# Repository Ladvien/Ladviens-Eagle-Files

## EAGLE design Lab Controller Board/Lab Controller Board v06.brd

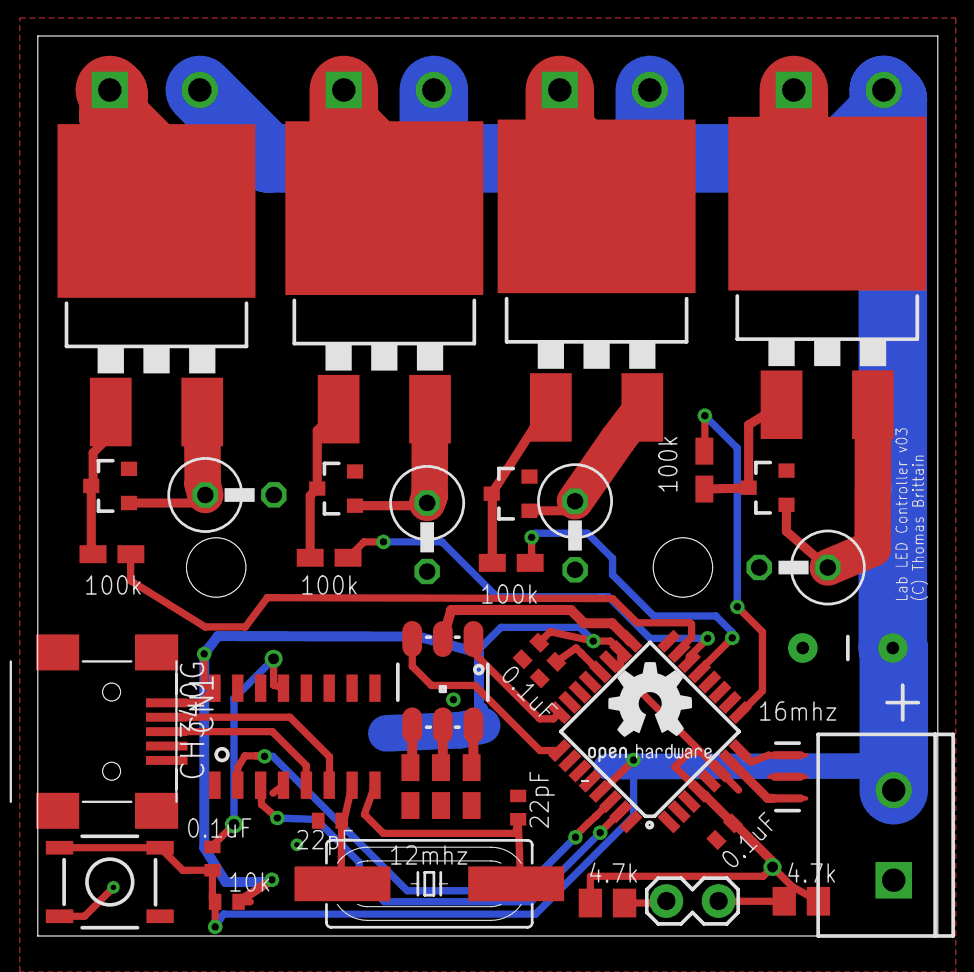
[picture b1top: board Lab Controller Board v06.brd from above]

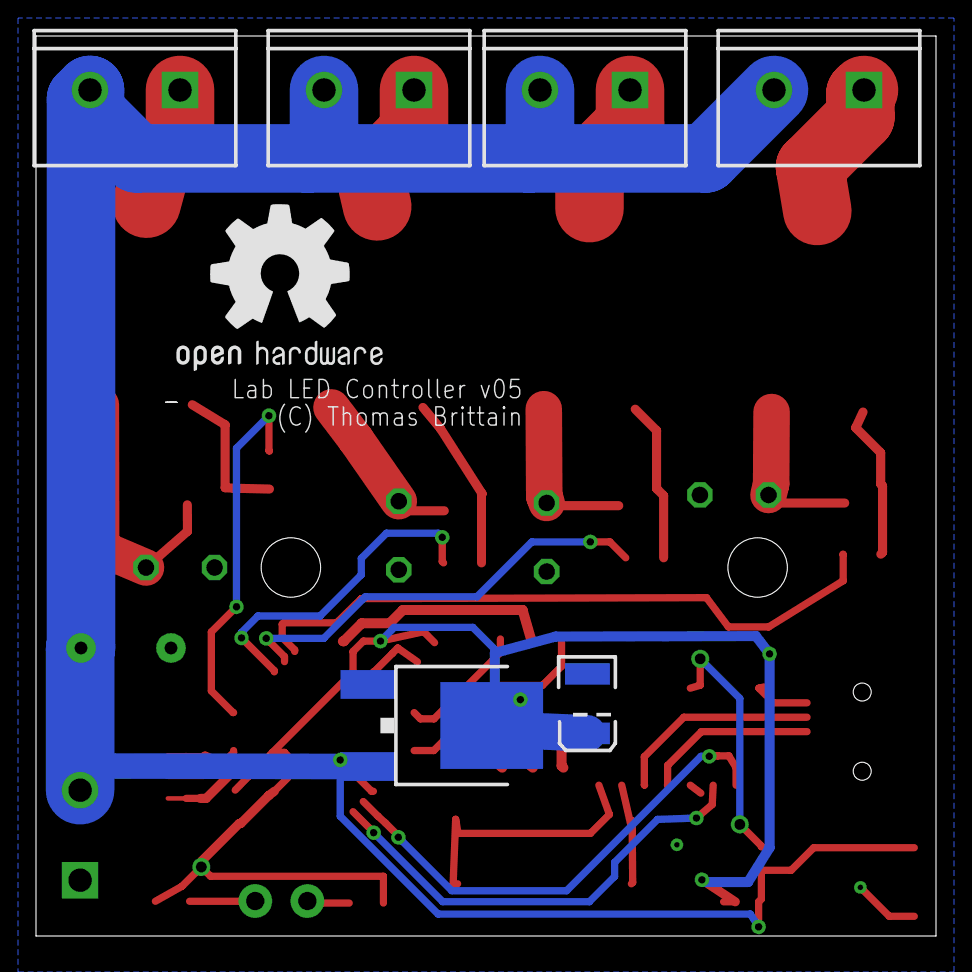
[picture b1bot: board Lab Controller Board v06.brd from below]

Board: 2 copper layers, 50.0 x 50.0 mm, 48 parts (7 on the bottom side), 38 nets.

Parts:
C1: big; CAP-PTH-5MM
C2: 10uF; EIA3528
C3, C4, C5, C8: 0.1uF; C0402
C6, C7: 22pF; C0402
CN1: USB-MINIB
FQP30N06L: 100A/100V; TO-263/D2PAK
GOLD_ORB_SM1: OSHWLOGO_GOLD_ORB_MED; OSHW1
GOLD_ORB_SM2: OSHWLOGO_GOLD_ORB_SM; OSHW2
JP1, JP2, JP3, JP4, JP5: SCREWTERMINAL-5MM-2
JP8: 1X02_LOCK
LED1: LED-TRICOLOR-5050NO_IC; LED-TRICOLOR-5050
MC7805CD2TR4: V_REG_MC33269DT; DPAK
Q1: HC49UP
Q2, Q4, Q6, Q8: MMBT5088; SOT23-3
Q3, Q5, Q7: 100A/100V; TO-263/D2PAK
R1, R3, R5, R7, R11, R12, R13: 100k; R0805W
R2, R4, R6, R8: .75Ohm; 0411V
R9, R10: 4.7k; M0805
R14: 10k; R0402
S1: TAC_SWITCHSMD; TACTILE-SWITCH-SMD
STANDOFF1, STANDOFF2: STAND-OFF
U1: ATMEGA328P_TQFP; TQFP32-08
U2: CH340G; SOIC16
Y1: 16MHZ; RESONATOR-SMD

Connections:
5: R5.1, U1.9
9: R7.1, U1.13
10: R1.1, U1.14
11: R3.1, U1.15
12V: C1.1, JP1.2, JP2.2, JP3.2, JP4.2, JP5.2, MC7805CD2TR4.3
13: LED1.2, U1.17
A1: LED1.1, U1.24
A2: LED1.3, U1.25
D+: CN1.D+, U2.5
D-: CN1.D-, U2.6
DTR: C5.1, U2.13
FET_SOURCE: FQP30N06L.3, Q2.1, R2.1
FET_SOURCE1: Q3.3, Q4.1, R4.1
FET_SOURCE2: Q5.3, Q6.1, R6.1
FET_SOURCE3: Q7.3, Q8.1, R8.1
GND: C1.2, C2.C, C3.2, C4.2, C6.2, C7.2, C8.2, CN1.GND, JP1.1, MC7805CD2TR4.1, Q2.2, Q4.2, Q6.2, Q8.2, R2.2, R4.2, R6.2, R8.2, R11.1, R12.1, R13.1, S1.1, S1.2, U1.3, U1.5, U1.21, U2.1, Y1.2
LED_DRAIN: FQP30N06L.2, JP2.1
LED_DRAIN1: JP5.1, Q3.2
LED_DRAIN2: JP4.1, Q5.2
LED_DRAIN3: JP3.1, Q7.2
unnamed: C3.1, U1.20
unnamed: U1.7, Y1.1
unnamed: LED1.4, R11.2
unnamed: LED1.6, R12.2
unnamed: LED1.5, R13.2
unnamed: U1.8, Y1.3
unnamed: C5.2, R14.1, S1.3, S1.4, U1.29
PWM_B: FQP30N06L.1, Q2.3, R1.2
PWM_B1: Q3.1, Q4.3, R3.2
PWM_B2: Q5.1, Q6.3, R5.2
PWM_B3: Q7.1, Q8.3, R7.2
SCL: JP8.1, R10.1
SDA: JP8.2, R9.1
U2_RX: U1.31, U2.3
U2_TX: U1.30, U2.2
VCC: C2.A, C4.1, C8.1, CN1.VBUS, MC7805CD2TR4.4, R9.2, R10.2, R14.2, U1.4, U1.6, U1.18, U2.16
X0: C7.1, Q1.2, U2.8
X1: C6.1, Q1.1, U2.7

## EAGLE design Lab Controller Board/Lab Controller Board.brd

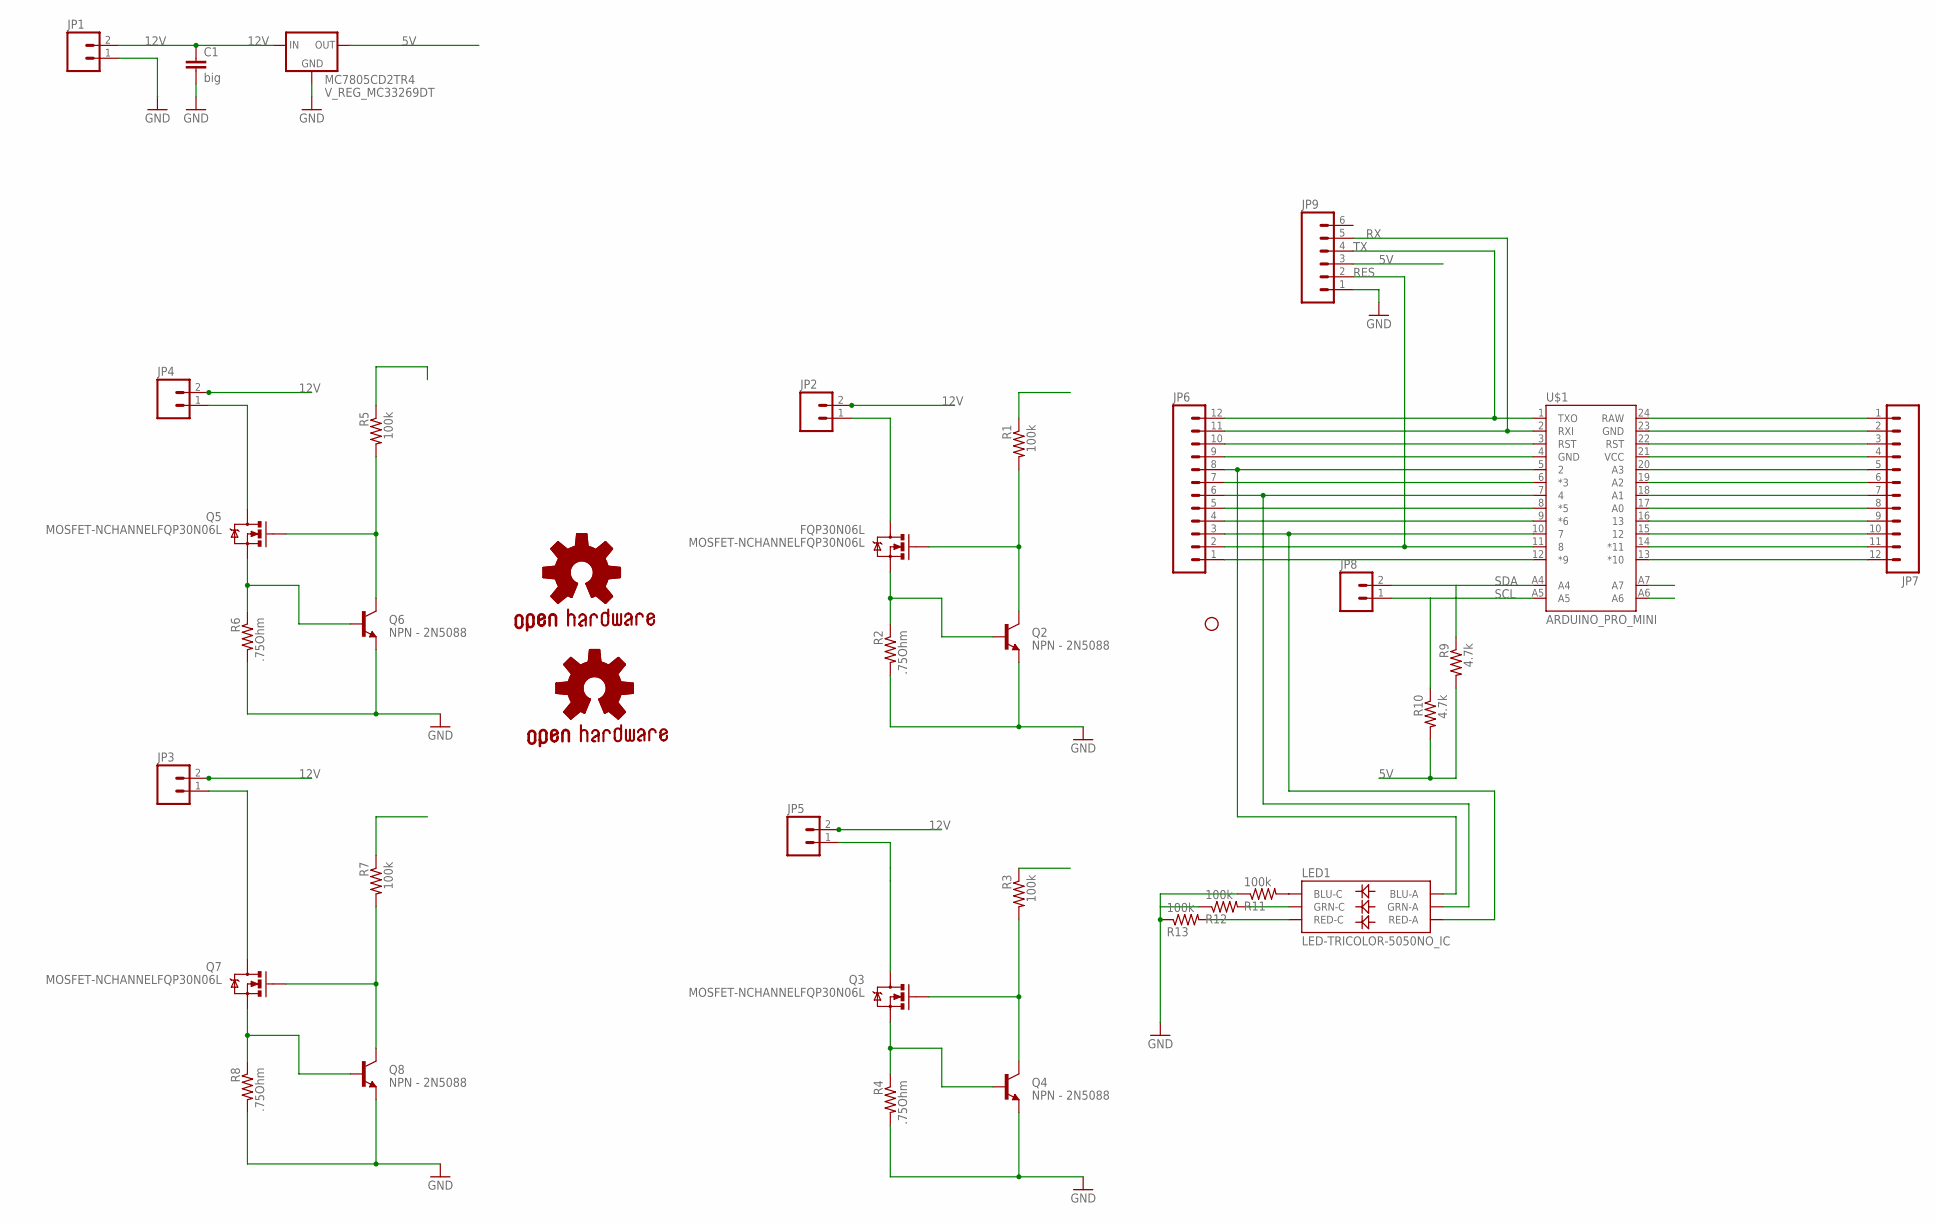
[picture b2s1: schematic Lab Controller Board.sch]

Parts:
C1: big; CAP-PTH-5MM
FQP30N06L: MOSFET-NCHANNELFQP30N06L; TO220V
GOLD_ORB_SM1: OSHWLOGO_GOLD_ORB_MED; OSHW1
GOLD_ORB_SM2: OSHWLOGO_GOLD_ORB_SM; OSHW2
JP1, JP2, JP3, JP4, JP5: M025MM; SCREWTERMINAL-5MM-2
JP6, JP7: M12PTH; 1X12
JP8: M02LOCK; 1X02_LOCK
JP9: M06LOCK; 1X06_LOCK
LED1: LED-TRICOLOR-5050NO_IC; LED-TRICOLOR-5050
MC7805CD2TR4: V_REG_MC33269DT; DPAK
Q2, Q4, Q6, Q8: NPN - 2N5088; TO-92
Q3, Q5, Q7: MOSFET-NCHANNELFQP30N06L; TO220V
R1, R3, R5, R7, R11, R12, R13: 100k; R0805W
R2, R4, R6, R8: .75Ohm; 0411V
R9, R10: 4.7k; M0805
STANDOFF1: STAND-OFF
U$1: ARDUINO_PRO_MINI

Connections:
5V: JP9.3, MC7805CD2TR4.4 (OUT), R9.2, R10.2
12V: C1.1, JP1.2, JP2.2, JP3.2, JP4.2, JP5.2, MC7805CD2TR4.3 (IN)
APM_PIN_3: JP6.7, R3.1, U$1.6 (*3)
APM_PIN_5: JP6.5, R1.1, U$1.8 (*5)
APM_PIN_6: JP6.4, R7.1, U$1.9 (*6)
APM_PIN_9: JP6.1, R5.1, U$1.12 (*9)
FET_SOURCE: FQP30N06L.3 (S), Q2.2 (B), R2.1
FET_SOURCE1: Q3.3 (S), Q4.2 (B), R4.1
FET_SOURCE2: Q5.3 (S), Q6.2 (B), R6.1
FET_SOURCE3: Q7.3 (S), Q8.2 (B), R8.1
GND: C1.2, JP1.1, JP9.1, MC7805CD2TR4.1 (GND), Q2.1 (E), Q4.1 (E), Q6.1 (E), Q8.1 (E), R2.2, R4.2, R6.2, R8.2, R11.1, R12.1, R13.1
LED_DRAIN: FQP30N06L.2 (D), JP2.1
LED_DRAIN1: JP5.1, Q3.2 (D)
LED_DRAIN2: JP4.1, Q5.2 (D)
LED_DRAIN3: JP3.1, Q7.2 (D)
unnamed: JP6.10, U$1.3 (RST)
unnamed: JP6.9, U$1.4 (GND)
unnamed: JP6.8, LED1.3 (BLU-A), U$1.5 (2)
unnamed: LED1.4 (BLU-C), R11.2
unnamed: JP6.6, LED1.1 (GRN-A), U$1.7 (4)
unnamed: LED1.6 (GRN-C), R12.2
unnamed: LED1.5 (RED-C), R13.2
unnamed: JP6.3, LED1.2 (RED-A), U$1.10 (7)
unnamed: JP7.1, U$1.24 (RAW)
unnamed: JP7.2, U$1.23 (GND)
unnamed: JP7.3, U$1.22 (RST)
unnamed: JP7.4, U$1.21 (VCC)
unnamed: JP7.5, U$1.20 (A3)
unnamed: JP7.6, U$1.19 (A2)
unnamed: JP7.7, U$1.18 (A1)
unnamed: JP7.8, U$1.17 (A0)
unnamed: JP7.9, U$1.16 (13)
unnamed: JP7.10, U$1.15 (12)
unnamed: JP7.11, U$1.14 (*11)
unnamed: JP7.12, U$1.13 (*10)
PWM_B: FQP30N06L.1 (G), Q2.3 (C), R1.2
PWM_B1: Q3.1 (G), Q4.3 (C), R3.2
PWM_B2: Q5.1 (G), Q6.3 (C), R5.2
PWM_B3: Q7.1 (G), Q8.3 (C), R7.2
RES: JP6.2, JP9.2, U$1.11 (8)
RX: JP6.11, JP9.5, U$1.2 (RXI)
SCL: JP8.1, R10.1, U$1.A5
SDA: JP8.2, R9.1, U$1.A4
TX: JP6.12, JP9.4, U$1.1 (TXO)

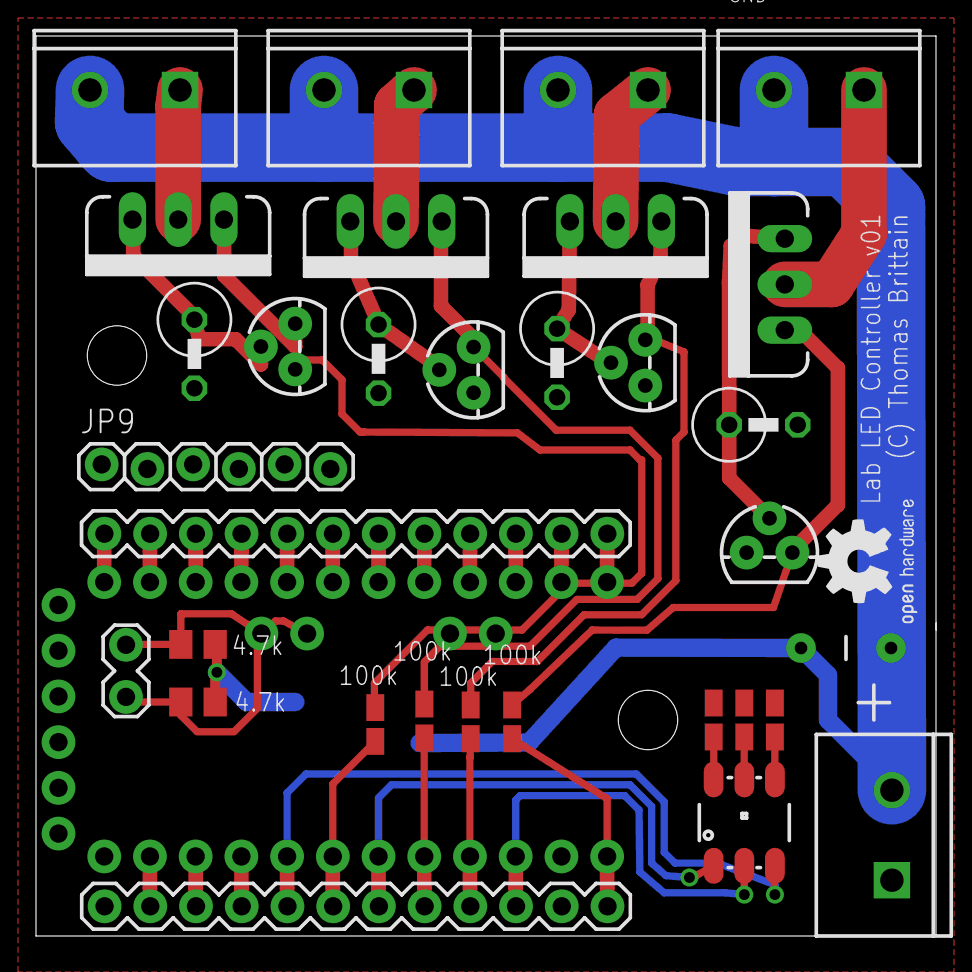
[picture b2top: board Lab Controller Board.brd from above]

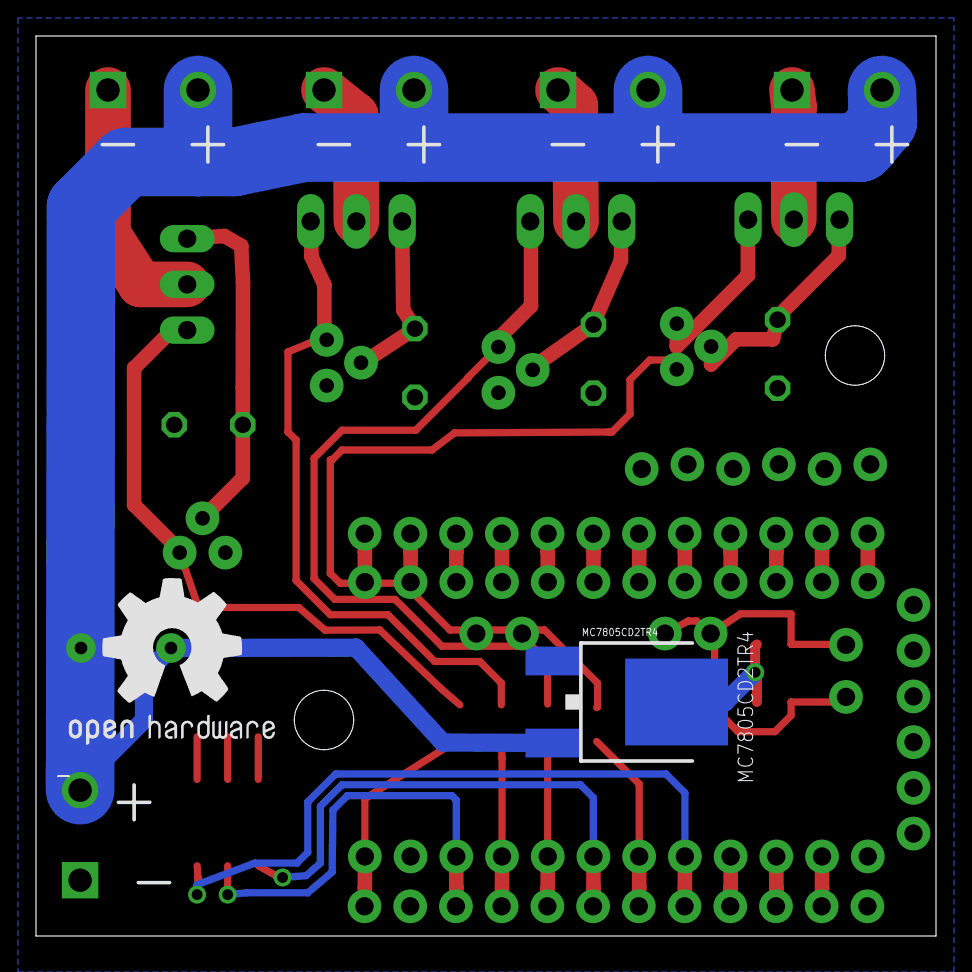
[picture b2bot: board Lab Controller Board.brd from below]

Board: 2 copper layers, 50.0 x 50.0 mm, 38 parts (2 on the bottom side), 44 nets.

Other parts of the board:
STANDOFF2: STAND-OFF

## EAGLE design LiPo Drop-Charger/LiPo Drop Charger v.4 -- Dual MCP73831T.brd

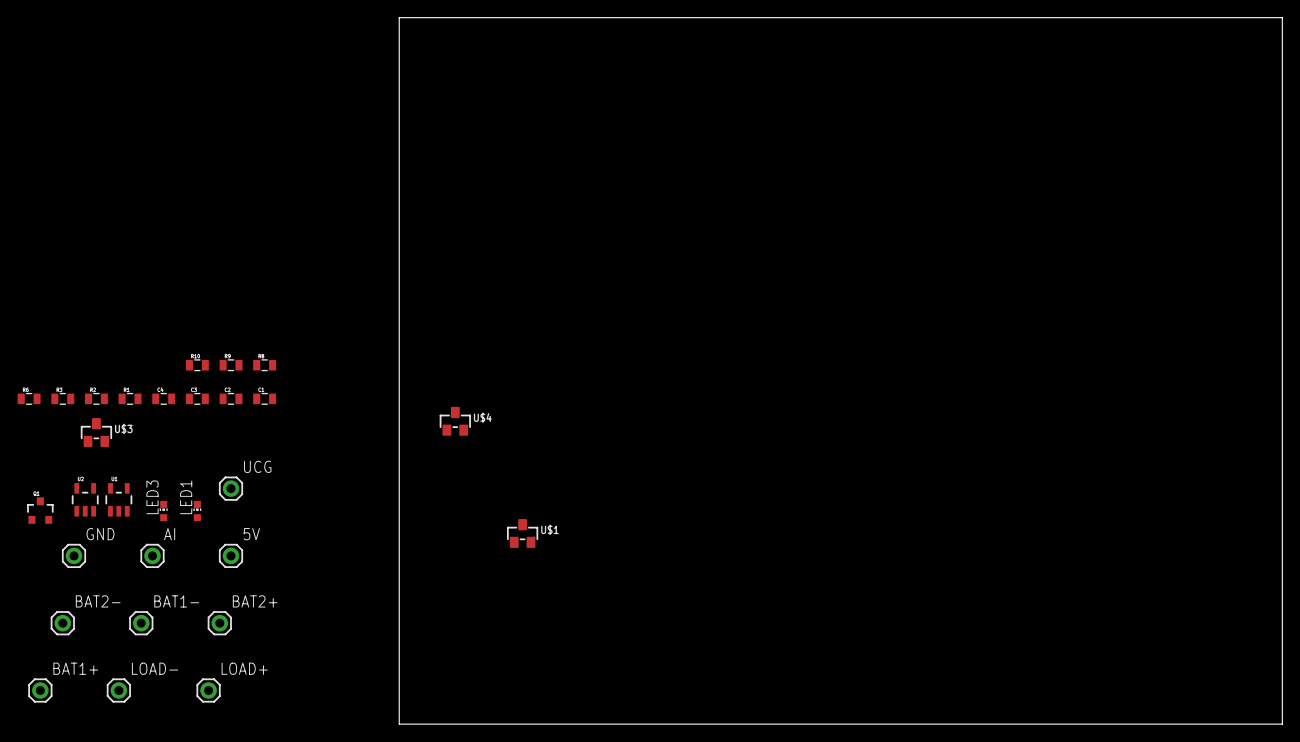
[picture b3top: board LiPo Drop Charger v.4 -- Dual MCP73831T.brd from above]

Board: 2 copper layers, 100.0 x 80.0 mm, 29 parts (0 on the bottom side), 13 nets, no tracks yet.

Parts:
5V: M01PTH; 1X01
AI: M01PTH; 1X01
BAT1+, BAT1-, BAT2+, BAT2-: M01PTH; 1X01
C1, C2, C3, C4: 1uF; 0805
GND: M01PTH; 1X01
LED1, LED3: CHIP-LED0603
LOAD+: M01PTH; 1X01
LOAD-: M01PTH; 1X01
Q1: ZXMN3F30FH; SOT23-3
R1, R2: 330; 0805
R3: 4.7; 0805
R6: 100k; 0805
R8, R9: 2K; 0805
R10: 1k; 0805
U1, U2: MCP73831; SOT23-5
U$1, U$3, U$4: DMP1045U; SOT-23
UCG: M01PTH; 1X01

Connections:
3.7OUT: BAT2-.1, U$1.3
3.7VIN: BAT1+.1, U$1.2, U$3.1, U$4.1, U$4.2
7.4V: BAT2+.1, LOAD+.1, U$3.2
+5V: 5V.1, C3.2, C4.2, LED1.A, LED3.A, Q1.1, R3.2, R6.1, R10.1, U1.4, U2.4, U$1.1
D: C1.2, C2.2, U1.3, U2.3, U$3.3, U$4.3
GND: C1.1, C2.1, C3.1, C4.1, GND.1, Q1.3, R6.2, R8.1, R9.1, R10.2, U1.2, U2.2, UCG.1
unnamed: AI.1, R1.1, R3.1, U1.1
unnamed: BAT1-.1, LOAD-.1
unnamed: R9.2, U1.5
unnamed: LED1.C, R1.2
unnamed: R8.2, U2.5
unnamed: LED3.C, R2.2
unnamed: R2.1, U2.1

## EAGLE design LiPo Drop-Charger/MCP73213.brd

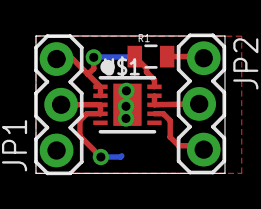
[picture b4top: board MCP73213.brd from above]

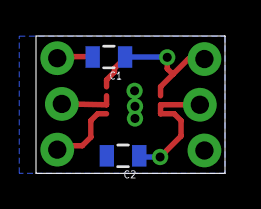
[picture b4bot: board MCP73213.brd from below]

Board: 2 copper layers, 10.5 x 7.6 mm, 6 parts (2 on the bottom side), 7 nets.

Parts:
C1, C2: 0805
JP1, JP2: 1X03_LOCK
R1: 2.32k; 0805
U$1: DFN10_3X3MM

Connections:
GND: C1.2, C2.2, JP1.1, U$1.GND
unnamed: C1.1, JP1.3, U$1.1, U$1.2
unnamed: C2.1, JP1.2, U$1.3, U$1.4
unnamed: R1.1, U$1.10
unnamed: JP2.1, R1.2
unnamed: JP2.2, U$1.8, U$1.9
unnamed: JP2.3, U$1.7

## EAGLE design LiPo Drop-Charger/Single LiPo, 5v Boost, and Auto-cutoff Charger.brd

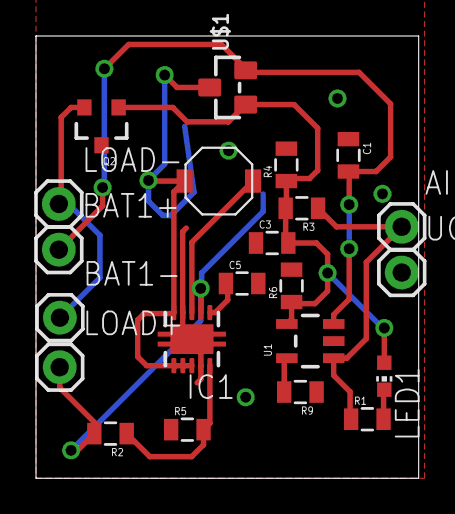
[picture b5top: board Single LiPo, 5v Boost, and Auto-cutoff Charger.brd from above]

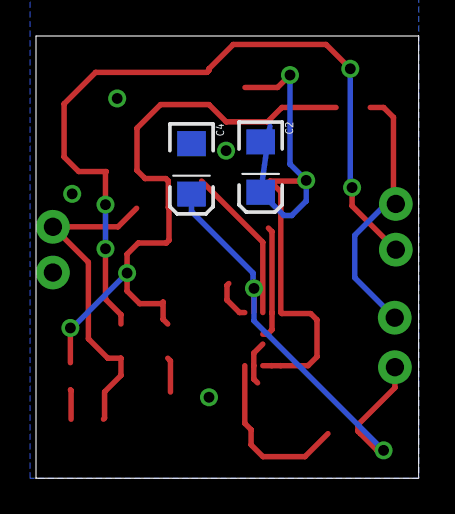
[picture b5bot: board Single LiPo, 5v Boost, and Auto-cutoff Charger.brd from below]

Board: 2 copper layers, 21.3 x 24.6 mm, 24 parts (2 on the bottom side), 12 nets.

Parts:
2.2UH: 2.2UH; VLF4012A
AI: M01PTH; 1X01
BAT1+, BAT1-: M01PTH; 1X01
C1, C3: 1uF; 0805
C2, C4: 10uF; EIA3216
C5: 0.1uF; 0805
IC1: TPS61200; S-PDSO-N10
LED1: CHIP-LED0603
LOAD+: M01PTH; 1X01
LOAD-: M01PTH; 1X01
Q2: ZXMN3F30FH; SOT23-3
R1: 330; 0805
R2: 1M; 0805
R3: 4.7; 0805
R4: 1k; 0805
R5: 180k; 0805
R6: 100k; 0805
R9: 2K; 0805
U1: MCP73831; SOT23-5
U$1: DMP1045U; SOT-23
UCG: M01PTH; 1X01

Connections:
3.7OUT: 2.2UH.P$1, C2.A, IC1.5, IC1.6, IC1.7, IC1.8, U$1.3
3.7VIN: BAT1+.1, C1.2, U1.3, U$1.2
+5V: C3.2, LED1.A, Q2.1, R3.2, R4.1, R6.1, U1.4, U$1.1
GND: C1.1, C2.C, C3.1, C4.C, C5.2, IC1.4, IC1.9, IC1.PP, IC1.PP@1, IC1.PP@2, Q2.3, R4.2, R5.1, R6.2, R9.1, U1.2, UCG.1
unnamed: C4.A, IC1.2, LOAD+.1, R2.2
unnamed: AI.1, R1.1, R3.1, U1.1
unnamed: BAT1-.1, LOAD-.1, Q2.2
unnamed: 2.2UH.P$2, IC1.3
unnamed: C5.1, IC1.1
unnamed: R9.2, U1.5
unnamed: LED1.C, R1.2
unnamed: IC1.10, R2.1, R5.2

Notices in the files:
parts and their libraries:
SparkFun-Connectors: Licensing: CC v3.0 Share-Alike You are welcome to use this library for commercial purposes.
SparkFun-Electromechanical: Licensing: Creative Commons ShareAlike 4.0 International - https://creativecommons.org/licenses/by-sa/4.0
